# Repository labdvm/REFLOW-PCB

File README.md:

# REFLOW-PCB
ReFlow PCB with ATtyny85
- Modification from " https://github.com/rallekralle11/Tinyreflow "
# J3 programming interface
- 1= +5Vcc
- 2= PB1_MISO
- 3= PB0_MOSI
- 4= PB2_SCK
- 5= GND
- 6= PB5_RST

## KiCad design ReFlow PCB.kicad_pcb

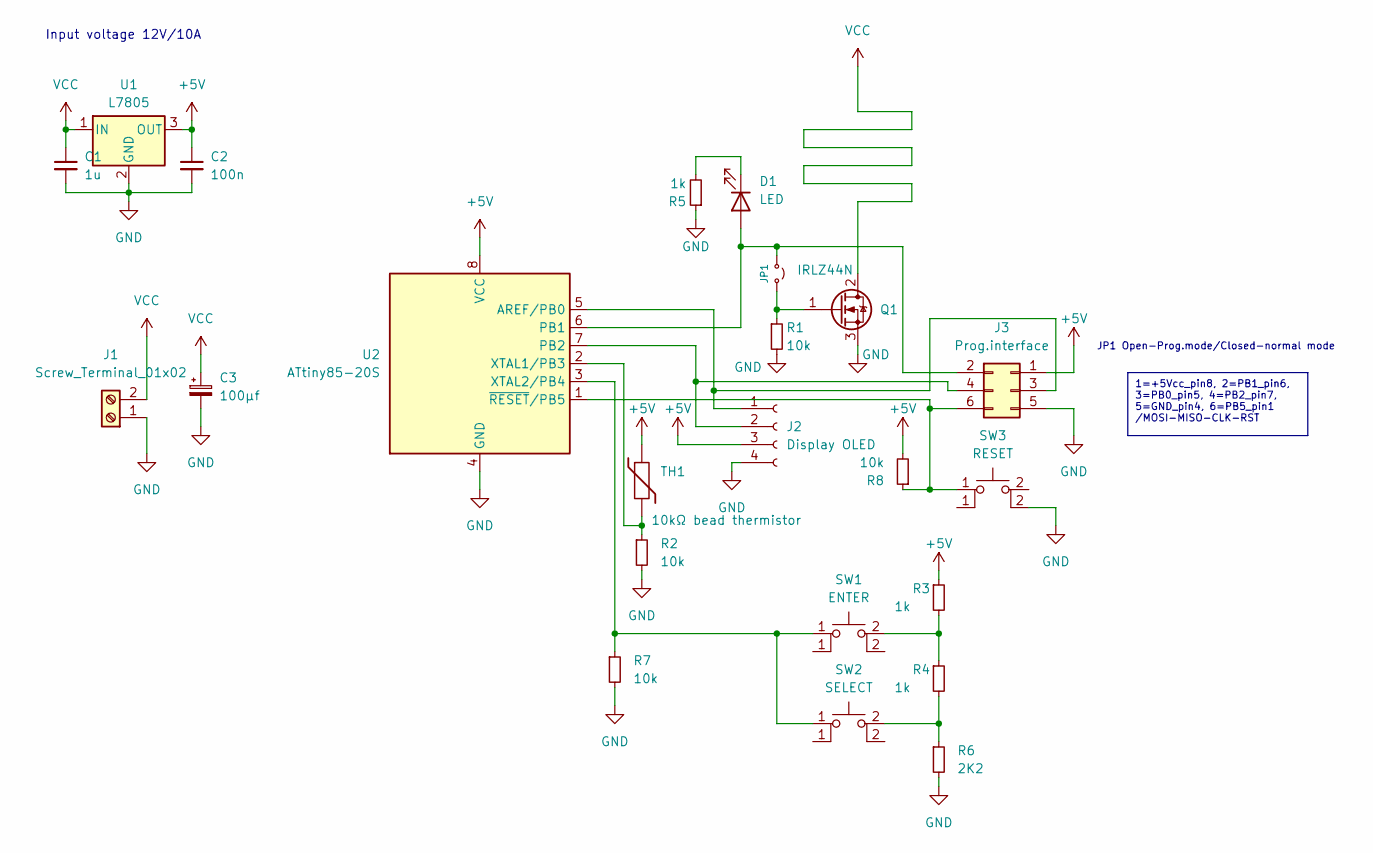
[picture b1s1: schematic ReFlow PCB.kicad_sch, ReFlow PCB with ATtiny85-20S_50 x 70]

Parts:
C1: 1u; C_1206_3216Metric
C2: 100n; C_1206_3216Metric
C3: 100µf; CP_Radial_D6.3mm_P2.50mm
D1: LED; LED_1206_3216Metric
J1: Screw_Terminal_01x02; TerminalBlock_Phoenix_MKDS-1,5-2-5.08_1x02_P5.08mm_Horizont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
J2: Display OLED; PinSocket_1x04_P2.54mm_Vertical
J3: Prog.interface; PinHeader_2x03_P2.54mm_Vertical
JP1: PinHeader_1x02_P2.54mm_Vertical
Q1: IRLZ44N; TO-220-3_Vertical
R1, R2, R7, R8: 10k; R_1206_3216Metric
R3, R4, R5: 1k; R_1206_3216Metric
R6: 2K2; R_1206_3216Metric
SW1: ENTER; SW_PUSH_6mm_H9.5mm
SW2: SELECT; SW_PUSH_6mm_H9.5mm
SW3: RESET; SW_PUSH_6mm_H9.5mm
TH1: 10kΩ bead thermistor; R_Axial_DIN0204_L3.6mm_D1.6mm_P2.54mm_Vertical
U1: L7805; TO-252-2
U2: ATtiny85-20S; SOIC-8_5.3x5.3mm_P1.27mm

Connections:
+5V: C2.1, J2.3, J3.1, R3.1, R8.2, TH1.1, U1.3 (OUT), U2.8 (VCC)
GND: C1.2, C2.2, C3.2, J1.1, J2.4, J3.5, Q1.3 (S), R1.2, R2.2, R5.1, R6.2, R7.2, SW3.2, U1.2 (GND), U2.4 (GND)
unnamed: D1.2 (A), J3.2, JP1.1 (A), U2.6 (PB1)
unnamed: D1.1 (K), R5.2
unnamed: J2.1, J3.3, U2.5 (AREF/PB0)
unnamed: J2.2, J3.4, U2.7 (PB2)
unnamed: J3.6, R8.1, SW3.1, U2.1 (~RESET/PB5)
unnamed: JP1.2 (B), Q1.1 (G), R1.1
unnamed: R3.2, R4.1, SW1.2
unnamed: R4.2, R6.1, SW2.2
unnamed: R2.1, TH1.2, U2.2 (XTAL1/PB3)
unnamed: R7.1, SW1.1, SW2.1, U2.3 (XTAL2/PB4)
VCC: C1.1, C3.1, J1.2, Q1.2 (D), U1.1 (IN)

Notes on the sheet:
Input voltage 12V/10A
JP1 Open-Prog.mode/Closed-normal mode
1=+5Vcc_pin8, 2=PB1_pin6, 3=PB0_pin5, 4=PB2_pin7, 5=GND_pin4, 6=PB5_pin1 /MOSI-MISO-CLK-RST

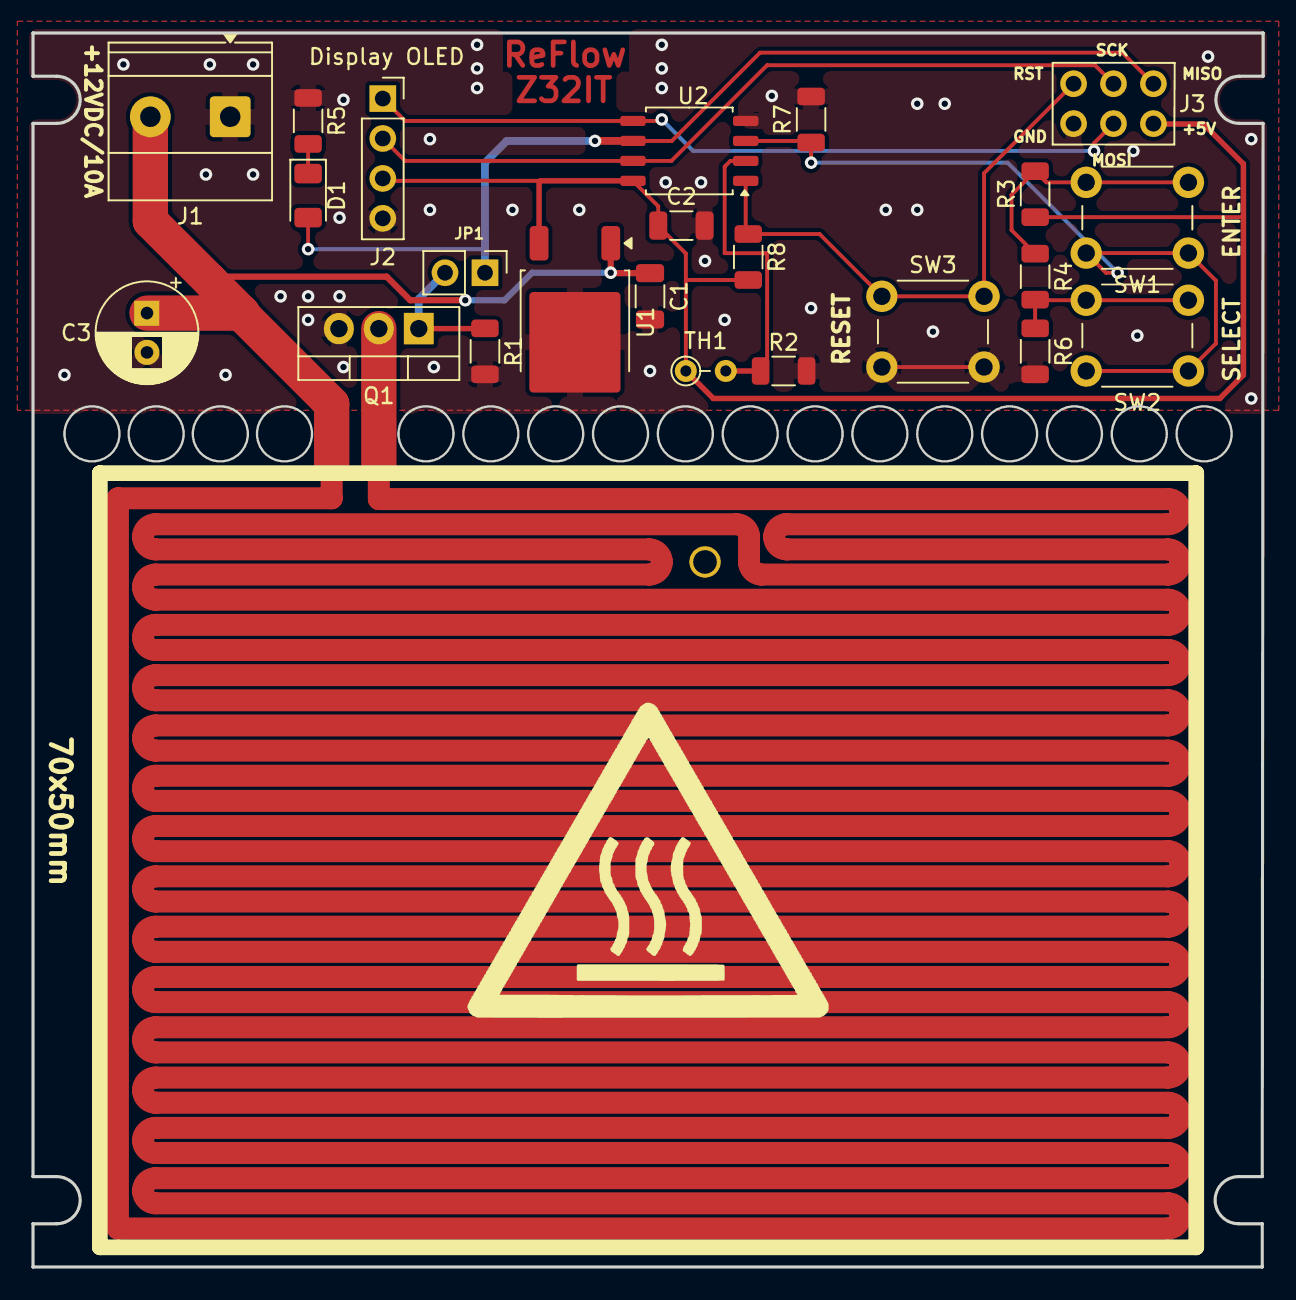
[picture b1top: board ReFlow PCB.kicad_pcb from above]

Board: 2 copper layers, 78.2 x 78.5 mm, 23 parts (0 on the bottom side), 13 nets.

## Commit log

2026-06-05 Update README with J3 programming interface
    Added J3 programming interface details to README.
2026-06-13 Add modification note to README
    Added modification note for reference to Tinyreflow project.
2026-06-13 Fix formatting in README.md
